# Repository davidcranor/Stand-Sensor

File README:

Stand-Sensor

Design files for accelerometer-based sitting/standing sensor and electrolaminate driver.  Built on Leaflabs' Maple.

Make sure that you have my hacked up version of the Wire library installed, as we need repeated start I2C. To install
it, make  backup of the old files and copy my Wire.cpp and Wire.h over them in the 

MapleIDE.app/Contents/Resources/Java/libraries/Wire/

directory (If you're on Mac).  This is a gross hack, sorry.
  
When uploading firmware, remember to build/install the Maple Mini target.

BOM is here:
https://docs.google.com/spreadsheet/ccc?key=0AkMyKIrUOd24dHlMcE16TWFrMjVCWlNEYzV1VXQ2dXc&usp=sharing

David Cranor
September 2013
cranor at media .mit dot edu

v1 notes/errata:

-DO NOT connect VCC-GND side of the switch when populating.
-USB port not close enough to edge on PCB
-Fix R12 to not trigger under-voltage protection when running off of battery power.  See datasheet for TPS61200.
-Fix mounting hole pattern to actually be symmetrical
-The leakage current in the currently specced D1 is too high, which caused some problems with the NFET power
 source switch.  Get one with a reasonable leakage current on next order.
-The PCB is slightly larger than the slot on the enclosure will allow.

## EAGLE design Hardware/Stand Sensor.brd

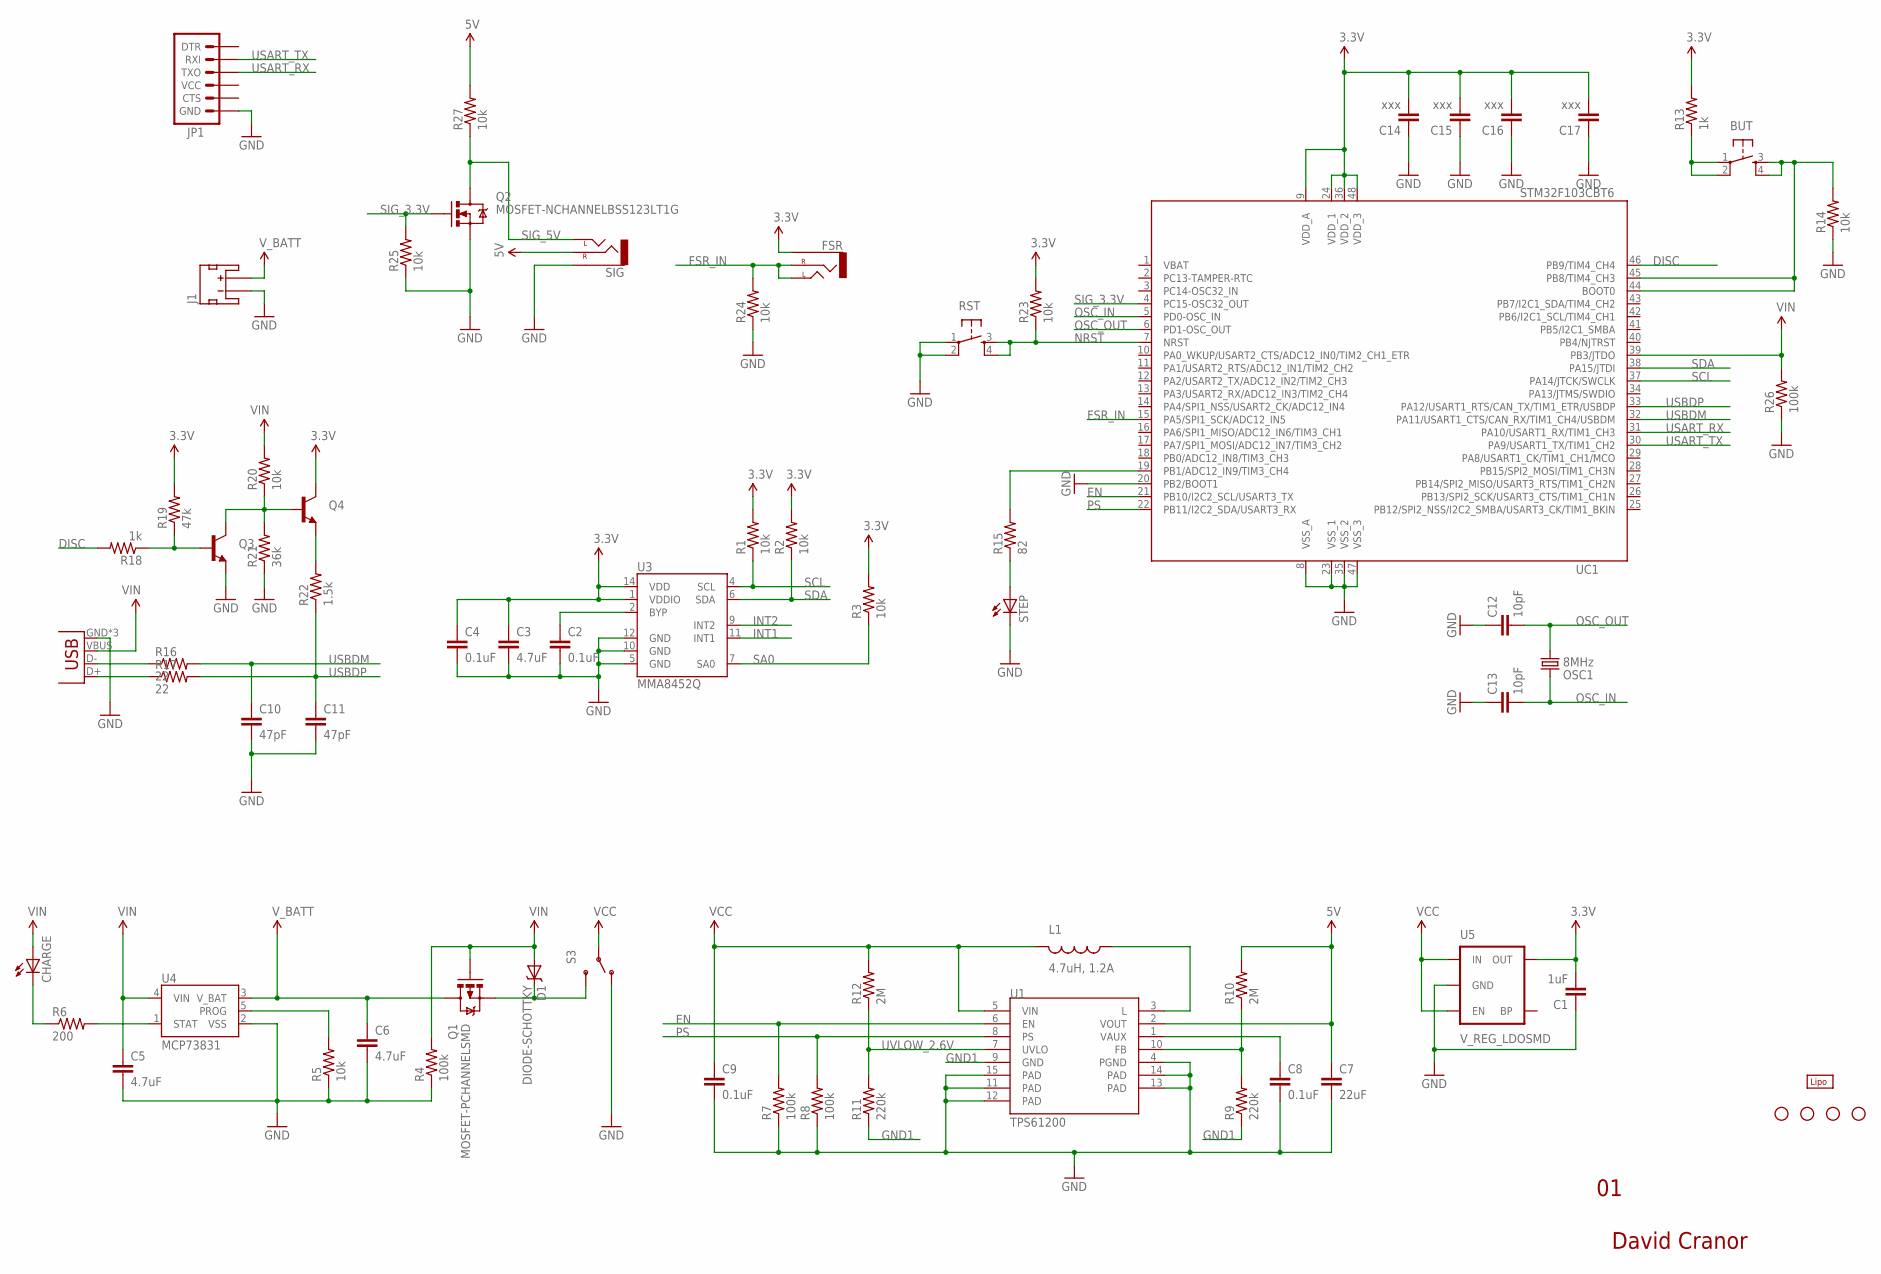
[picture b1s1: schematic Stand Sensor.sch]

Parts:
BUT: TAC_SWITCHSMD; TACTILE_SWITCH_SMD
C1: 1uF; 1206
C2, C4, C8, C9: 0.1uF; 1206
C3, C5, C6: 4.7uF; 1206
C7: 22uF; 1206
C10, C11: 47pF; 1206
C12, C13: 10pF; 1206
C14, C15, C16, C17: xxx; 1206
CHARGE: LED1206; LED-1206
D1: DIODE-SCHOTTKY; SOD-523
FSR: AUDIO-JACKPTH; AUDIO-JACK
J1: JST_2MM_MALE; JST-2-SMD
JP1: ARDUINO_SERIAL_PROGRAMSMD; 1X06-SMD
L1: 4.7uH, 1.2A; CDRH2D09
OSC1: 8MHz; CRYSTAL-SMD-5X3
Q1: MOSFET-PCHANNELSMD; SOT23-3
Q2: MOSFET-NCHANNELBSS123LT1G; SOT23
Q3, Q4: TRANSISTOR_NPNSOT23; SOT23
R1, R2, R3, R5, R14, R20, R23, R24, R25, R27: 10k; 1206
R4, R7, R8, R26: 100k; 1206
R6: 200; 1206
R9, R11: 220k; 1206
R10, R12: 2M; 1206
R13, R18: 1k; 1206
R15: 82; 1206
R16, R17: 22; 1206
R19: 47k; 1206
R21: 36k; 1206
R22: 1.5k; 1206
RST: TAC_SWITCHSMD; TACTILE_SWITCH_SMD
S3: SWITCH-SPDTSMD; AYZ0202
SIG: AUDIO-JACKPTH; AUDIO-JACK
STANDOFF1, STANDOFF2, STANDOFF3, STANDOFF4: STAND-OFF
STEP: LED1206; LED-1206
U1: TPS61200; QFN-10_PAD
U3: MMA8452Q; QFN-16_0.5MM
U4: MCP73831; SOT23-5
U5: V_REG_LDOSMD; SOT23-5
U$1: LIPO-OUTLINE2000; LIPO-2000
UC1: STM32F103CBT6; LQFP48
USB: USB-MICROB

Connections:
3.3V: C1.2, C3.1, C4.1, C14.2, C15.2, C16.2, C17.2, FSR.SLEEVE, Q4.3 (C), R1.2, R2.2, R3.2, R13.2, R19.2, R23.2, U3.1 (VDDIO), U3.14 (VDD), U5.5 (OUT), UC1.9 (VDD_A), UC1.24 (VDD_1), UC1.36 (VDD_2), UC1.48 (VDD_3)
5V: C7.1, R10.2, R27.2, SIG.RING (RIGHT), U1.2 (VOUT)
D+: R17.1, USB.D+
D-: R16.1, USB.D-
DISC: R18.2, UC1.46 (PB9/TIM4_CH4)
EN: R7.2, U1.6 (EN), UC1.21 (PB10/I2C2_SCL/USART3_TX)
FSR_IN: FSR.RING (RIGHT), FSR.TIP (LEFT), R24.2, UC1.15 (PA5/SPI1_SCK/ADC12_IN5)
GND: C1.1, C2.2, C3.2, C4.2, C5.2, C6.2, C7.2, C8.2, C9.2, C10.2, C11.2, C12.1, C13.1, C14.1, C15.1, C16.1, C17.1, J1.1 (-), JP1.6 (GND), Q2.2 (S), Q3.2 (E), R4.1, R5.1, R7.1, R8.1, R14.1, R21.1, R24.1, R25.1, R26.1, RST.1, RST.2, S3.1 (O), SIG.SLEEVE, STEP.C, U1.4 (PGND), U1.11 (PAD), U1.12 (PAD), U1.13 (PAD), U1.14 (PAD), U1.15 (PAD), U3.5 (GND), U3.10 (GND), U3.12 (GND), U4.2 (VSS), U5.2 (GND), UC1.8 (VSS_A), UC1.20 (PB2/BOOT1), UC1.23 (VSS_1), UC1.35 (VSS_2), UC1.47 (VSS_3), USB.GND, USB.MT1 (GND), USB.MT2 (GND)
GND1: R9.1, R11.1, U1.9 (GND)
INT1: U3.11 (INT1)
INT2: U3.9 (INT2)
unnamed: C2.1, U3.2 (BYP)
unnamed: L1.P$1 (1), U1.3 (L)
unnamed: R5.2, U4.5 (PROG)
unnamed: R6.2, U4.1 (STAT)
unnamed: CHARGE.C, R6.1
unnamed: D1.C, Q1.2 (S), S3.3 (S)
unnamed: C8.1, U1.1 (VAUX)
unnamed: R9.2, R10.1, U1.10 (FB)
unnamed: R15.2, UC1.19 (PB1/ADC12_IN9/TIM3_CH4)
unnamed: BUT.3, BUT.4, R14.2, UC1.44 (BOOT0), UC1.45 (PB8/TIM4_CH3)
unnamed: R15.1, STEP.A
unnamed: BUT.1, BUT.2, R13.1
unnamed: Q3.1 (B), R18.1, R19.1
unnamed: Q3.3 (C), Q4.1 (B), R20.1, R21.2
unnamed: Q4.2 (E), R22.2
NRST: R23.1, RST.3, RST.4, UC1.7 (NRST)
OSC_IN: C13.2, OSC1.3 (2), UC1.5 (PD0-OSC_IN)
OSC_OUT: C12.2, OSC1.1, UC1.6 (PD1-OSC_OUT)
PS: R8.2, U1.8 (PS), UC1.22 (PB11/I2C2_SDA/USART3_RX)
SA0: R3.1, U3.7 (SA0)
SCL: R1.1, U3.4 (SCL), UC1.37 (PA14/JTCK/SWCLK)
SDA: R2.1, U3.6 (SDA), UC1.38 (PA15/JTDI)
SIG_3.3V: Q2.1 (G), R25.2, UC1.4 (PC15-OSC32_OUT)
SIG_5V: Q2.3 (D), R27.1, SIG.TIP (LEFT)
USART_RX: JP1.3 (TXO), UC1.31 (PA10/USART1_RX/TIM1_CH3)
USART_TX: JP1.2 (RXI), UC1.30 (PA9/USART1_TX/TIM1_CH2)
USBDM: C10.1, R16.2, UC1.32 (PA11/USART1_CTS/CAN_RX/TIM1_CH4/USBDM)
USBDP: C11.1, R17.2, R22.1, UC1.33 (PA12/USART1_RTS/CAN_TX/TIM1_ETR/USBDP)
UVLOW_2.6V: R11.2, R12.1, U1.7 (UVLO)
VBAT: UC1.1 (VBAT)
VCC: C9.1, L1.P$2 (2), R12.2, S3.2, U1.5 (VIN), U5.1 (IN), U5.3 (EN)
VIN: C5.1, CHARGE.A, D1.A, Q1.1 (G), R4.2, R20.2, R26.2, U4.4 (VIN), UC1.39 (PB3/JTDO), USB.VBUS
V_BATT: C6.1, J1.2 (+), Q1.3 (D), U4.3 (V_BAT)

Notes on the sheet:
David Cranor

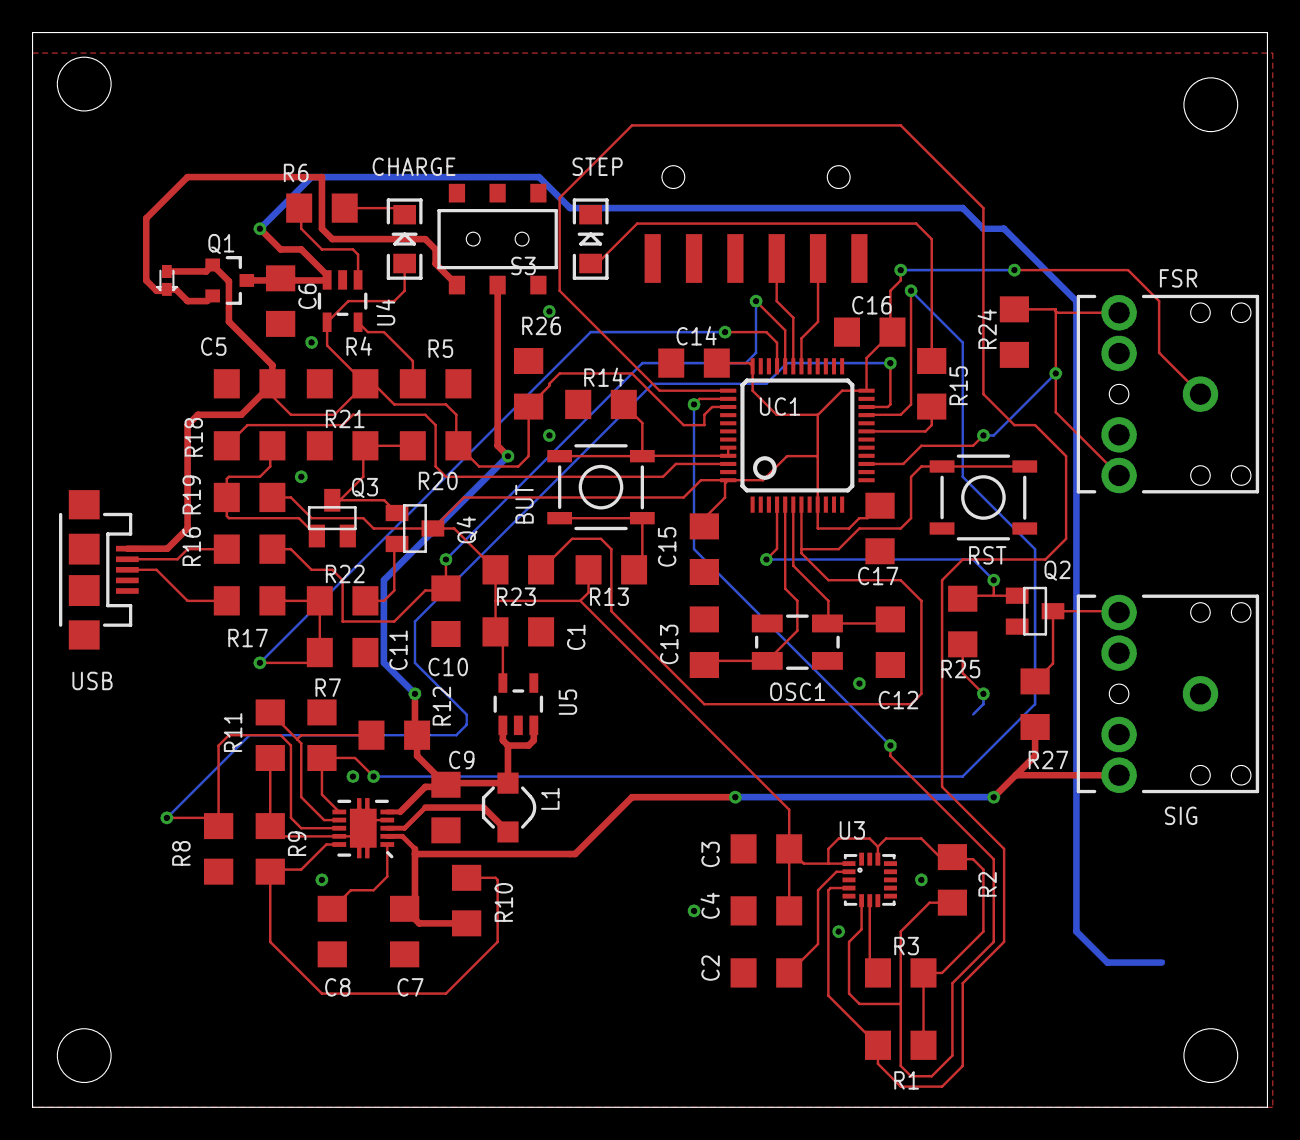
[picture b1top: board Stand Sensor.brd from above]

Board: 2 copper layers, 75.9 x 66.0 mm, 71 parts (1 on the bottom side), 41 nets.

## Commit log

2013-09-20 formatting
2013-09-20 formatting README

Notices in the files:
parts and their libraries:
SparkFun-PowerIC: Licensing: CC v3.0 Share-Alike You are welcome to use this library for commercial purposes.
